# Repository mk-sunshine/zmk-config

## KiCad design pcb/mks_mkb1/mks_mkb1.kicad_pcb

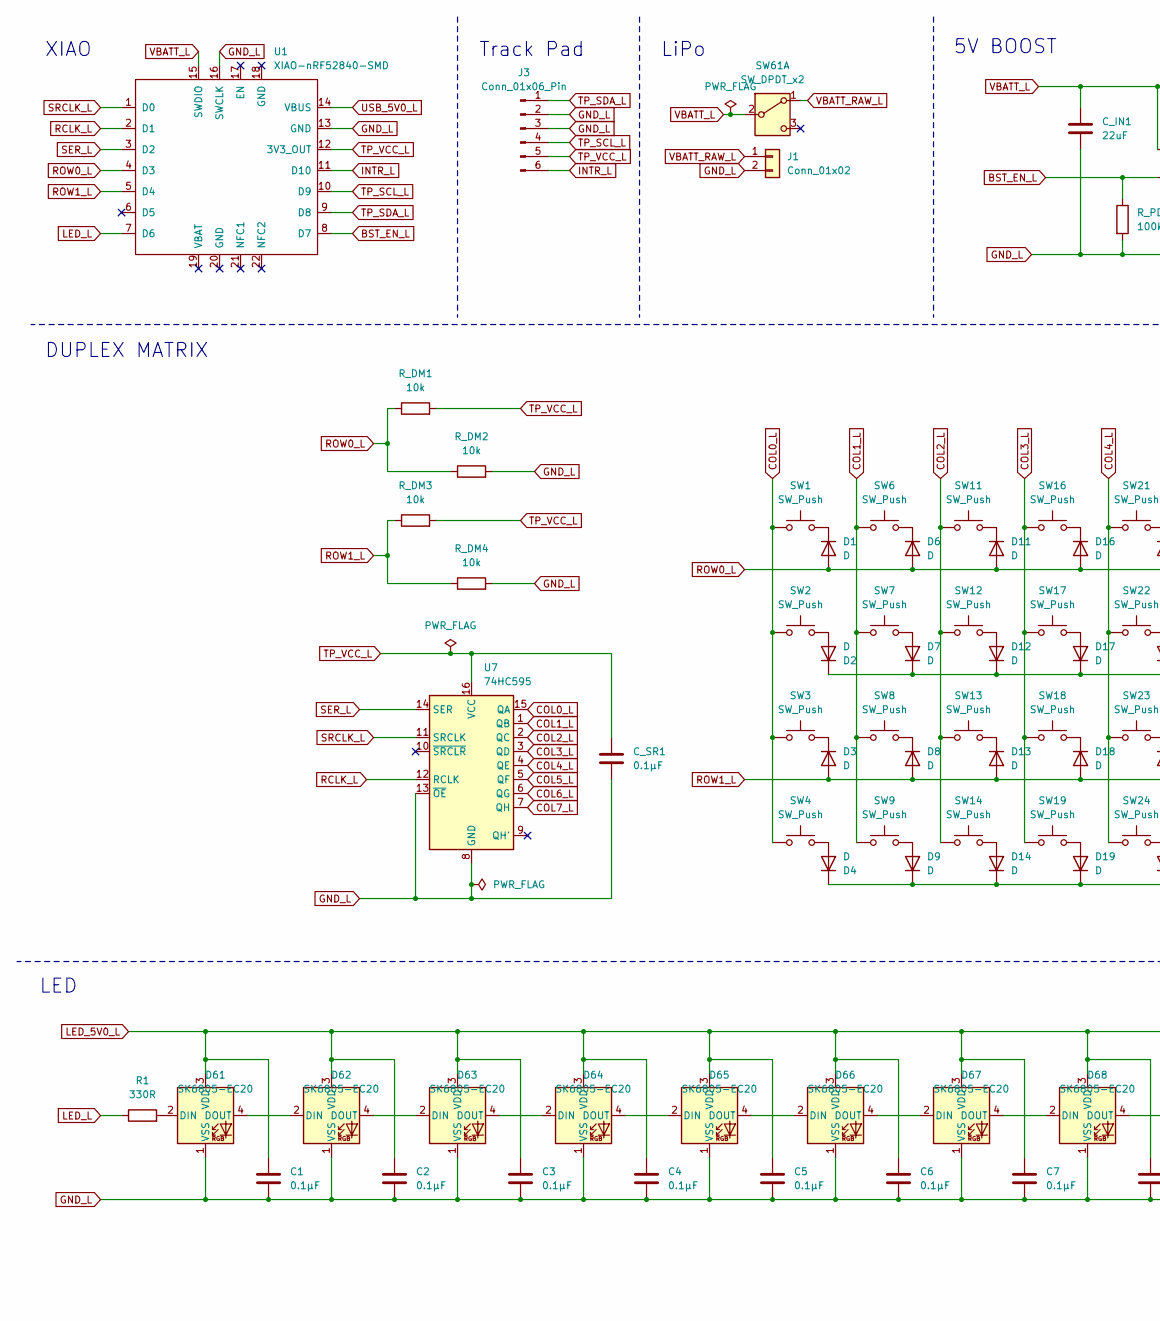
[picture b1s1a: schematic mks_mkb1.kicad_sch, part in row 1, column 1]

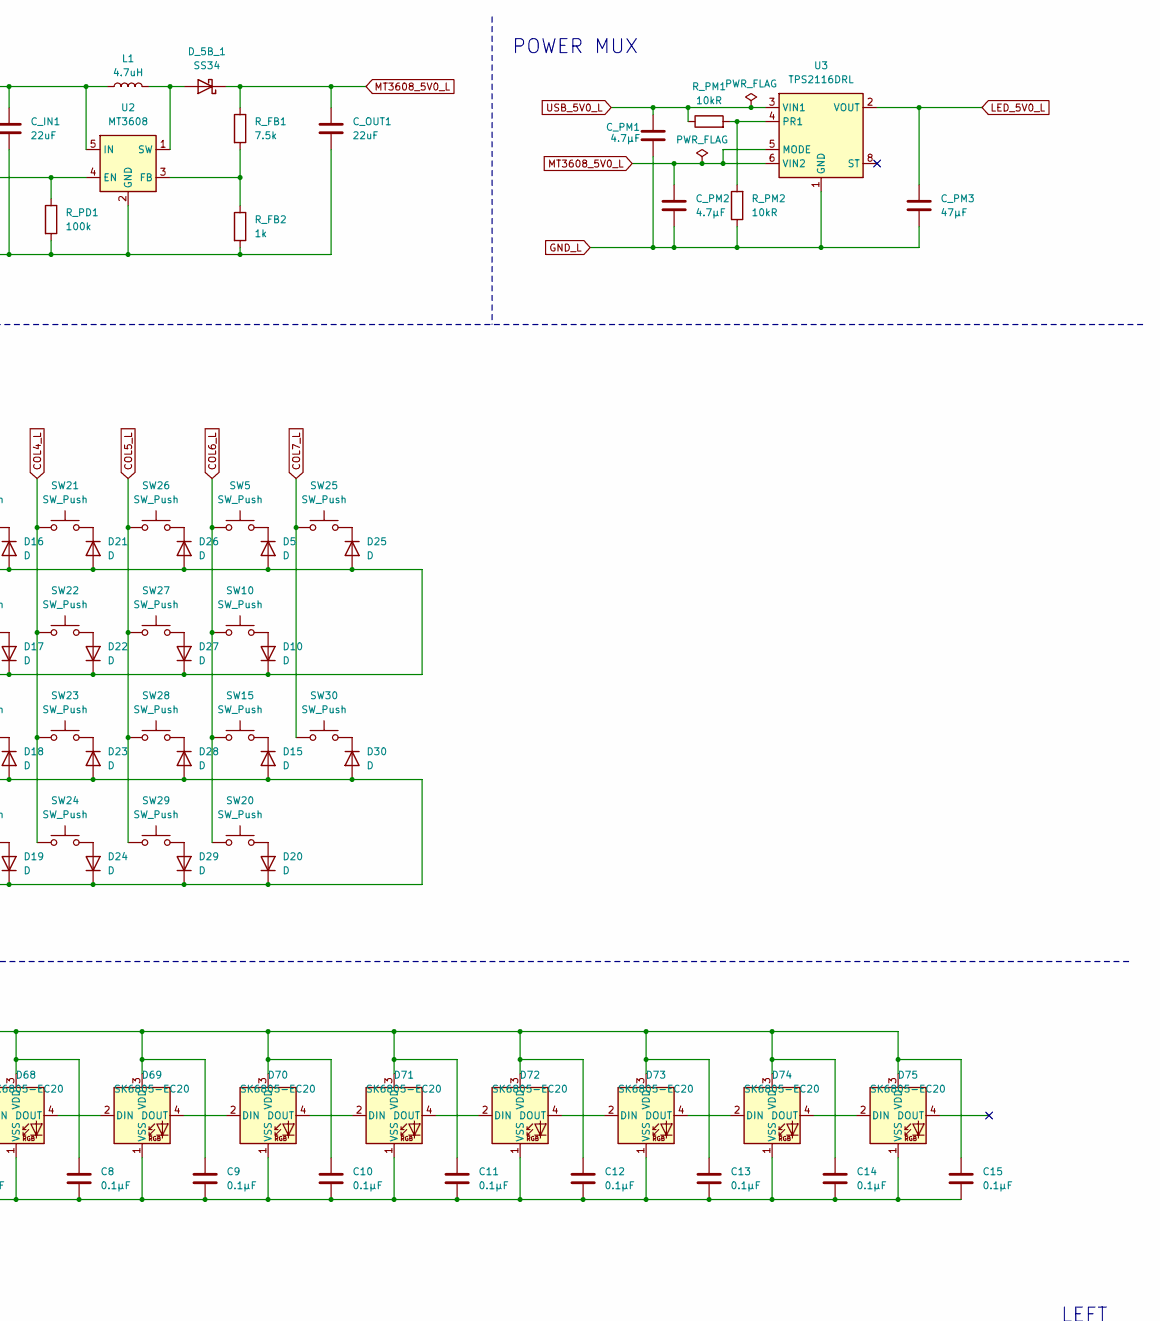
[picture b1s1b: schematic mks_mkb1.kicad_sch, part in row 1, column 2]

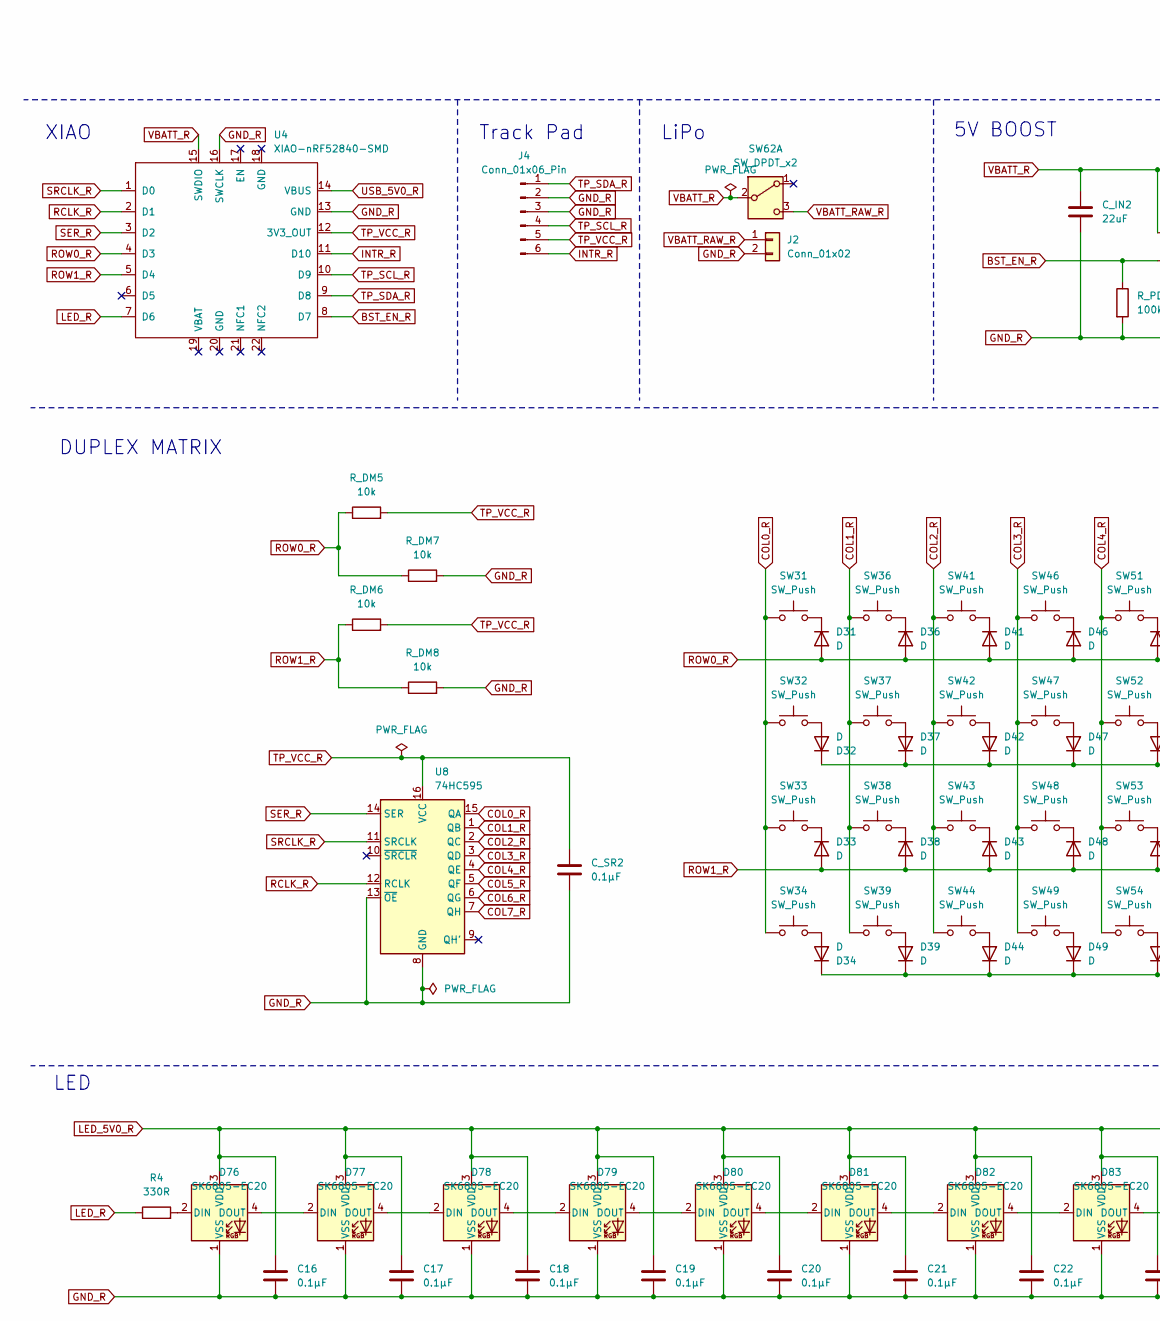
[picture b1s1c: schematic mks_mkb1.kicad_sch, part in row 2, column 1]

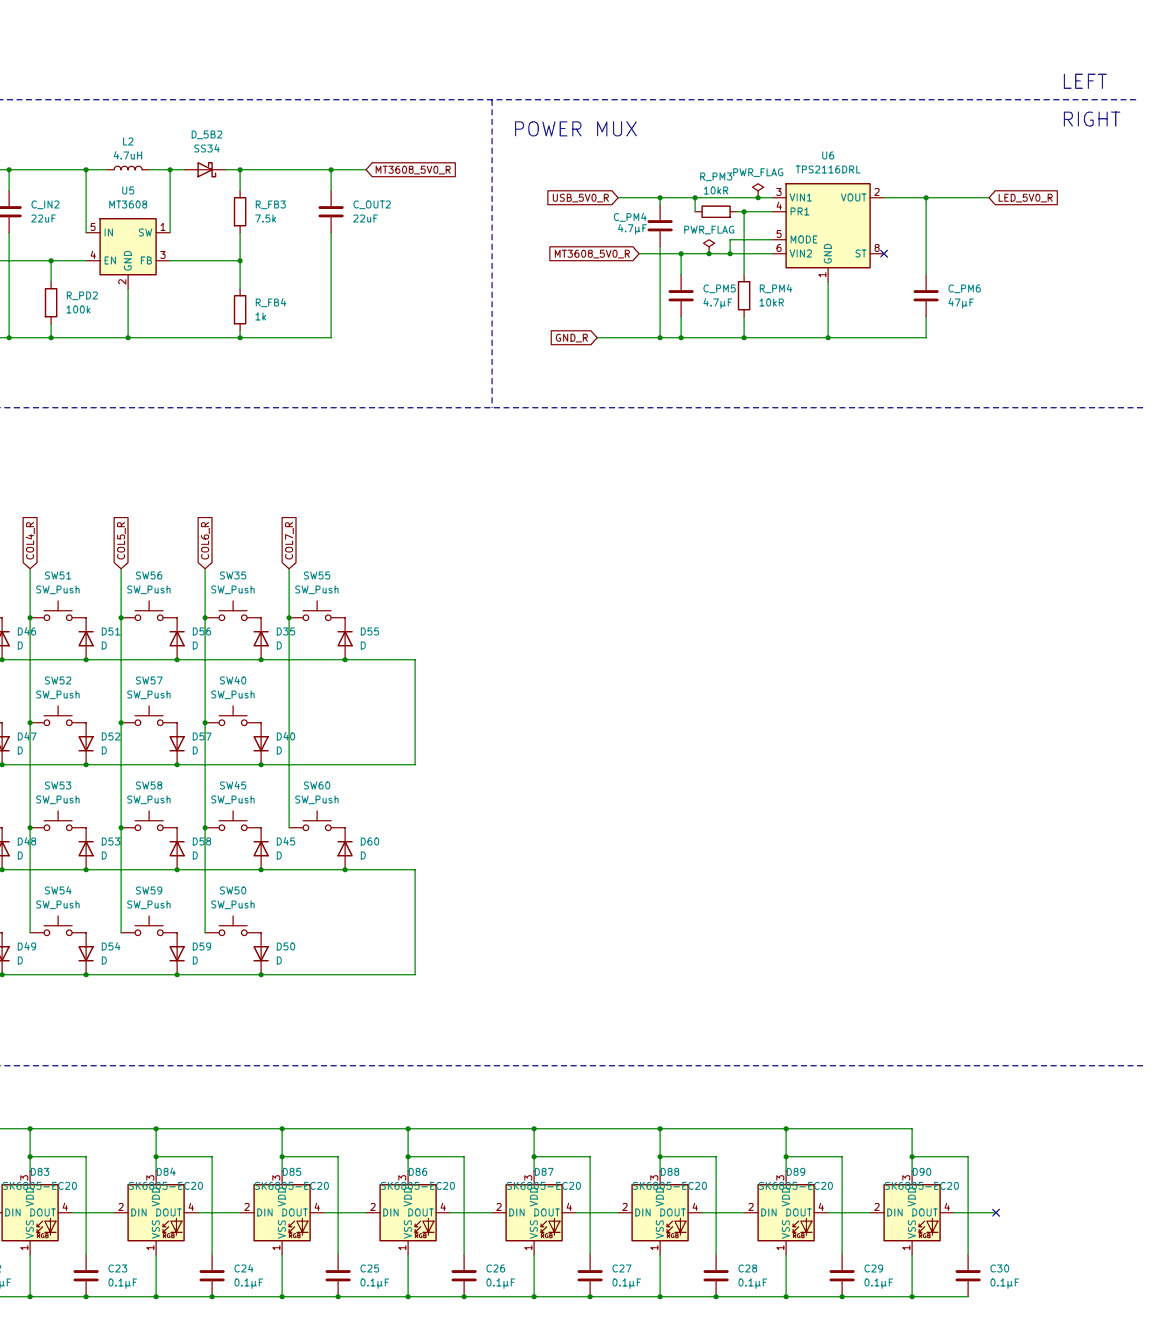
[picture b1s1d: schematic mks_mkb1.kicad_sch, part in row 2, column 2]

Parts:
C1, C2, C3, C4, C5, C6, C7, C8, C9, C10, C11, C12, C13, C14, C15, C16, C17, C18, C19, C20, C21, C22, C23, C24, C25, C26, C27, C28, C29, C30: 0.1µF; C_0603_1608Metric; LCSC C14663
C_IN1, C_IN2: 22uF; C_0805_2012Metric; LCSC C45783
C_OUT1, C_OUT2: 22uF; C_0805_2012Metric; LCSC C45783
C_PM1, C_PM2, C_PM4, C_PM5: 4.7µF; C_0603_1608Metric; LCSC C19666
C_PM3, C_PM6: 47µF; C_0603_1608Metric; LCSC C15852
C_SR1, C_SR2: 0.1µF; C_0603_1608Metric; LCSC C14663
D1, D2, D3, D4, D5, D6, D7, D8, D9, D10, D11, D12, D13, D14, D15, D16, D17, D18, D19, D20, D21, D22, D23, D24, D25, D26, D27, D28, D29, D30, D31, D32, D33, D34, D35, D36, D37, D38, D39, D40, D41, D42, D43, D44, D45, D46, D47, D48, D49, D50, D51, D52, D53, D54, D55, D56, D57, D58, D59, D60: D; D_SOD-123; LCSC C81598
D61, D62, D63, D64, D65, D66, D67, D68, D69, D70, D71, D72, D73, D74, D75, D76, D77, D78, D79, D80, D81, D82, D83, D84, D85, D86, D87, D88, D89, D90: SK6805-EC20
D_5B2, D_5B_1: SS34; D_SMA
J1, J2: Conn_01x02; JST_PH_S2B-PH-K_1x02_P2.00mm_Horizontal
J3, J4: Conn_01x06_Pin; PinSocket_2x03_P2.54mm_Vertical
L1, L2: 4.7uH; L_1210_3225Metric
R1, R4: 330R; R_0603_1608Metric; LCSC C23138
R_DM1, R_DM2, R_DM3, R_DM4, R_DM5, R_DM6, R_DM7, R_DM8: 10k; R_0603_1608Metric; LCSC C25804
R_FB1, R_FB3: 7.5k; R_0603_1608Metric; LCSC C23234
R_FB2, R_FB4: 1k; R_0603_1608Metric; LCSC C21190
R_PD1, R_PD2: 100k; R_0603_1608Metric; LCSC C25803
R_PM1, R_PM2, R_PM3, R_PM4: 10kR; R_0603_1608Metric; LCSC C25804
SW1, SW2, SW3, SW4, SW5, SW6, SW7, SW8, SW9, SW10, SW11, SW12, SW13, SW14, SW15, SW16, SW17, SW18, SW19, SW20, SW21, SW22, SW23, SW24, SW25, SW26, SW27, SW28, SW29, SW30, SW31, SW32, SW33, SW34, SW35, SW36, SW37, SW38, SW39, SW40, SW41, SW42, SW43, SW44, SW45, SW46, SW47, SW48, SW49, SW50, SW51, SW52, SW53, SW54, SW55, SW56, SW57, SW58, SW59, SW60: SW_Push; SW_Kailh_Choc_V1
SW61, SW62: SW_DPDT_x2
U1, U4: XIAO-nRF52840-SMD
U2, U5: MT3608; SOT-23-6
U3, U6: TPS2116DRL; SOT-583-8
U7, U8: 74HC595; SOIC-16_3.9x9.9mm_P1.27mm

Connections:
BST_EN_L: R_PD1.1, U1.8 (D7), U2.4 (EN)
BST_EN_R: R_PD2.1, U4.8 (D7), U5.4 (EN)
COL0_L: SW1.1, SW2.1, SW3.1, SW4.1, U7.15 (QA)
COL0_R: SW31.1, SW32.1, SW33.1, SW34.1, U8.15 (QA)
COL1_L: SW6.1, SW7.1, SW8.1, SW9.1, U7.1 (QB)
COL1_R: SW36.1, SW37.1, SW38.1, SW39.1, U8.1 (QB)
COL2_L: SW11.1, SW12.1, SW13.1, SW14.1, U7.2 (QC)
COL2_R: SW41.1, SW42.1, SW43.1, SW44.1, U8.2 (QC)
COL3_L: SW16.1, SW17.1, SW18.1, SW19.1, U7.3 (QD)
COL3_R: SW46.1, SW47.1, SW48.1, SW49.1, U8.3 (QD)
COL4_L: SW21.1, SW22.1, SW23.1, SW24.1, U7.4 (QE)
COL4_R: SW51.1, SW52.1, SW53.1, SW54.1, U8.4 (QE)
COL5_L: SW26.1, SW27.1, SW28.1, SW29.1, U7.5 (QF)
COL5_R: SW56.1, SW57.1, SW58.1, SW59.1, U8.5 (QF)
COL6_L: SW5.1, SW10.1, SW15.1, SW20.1, U7.6 (QG)
COL6_R: SW35.1, SW40.1, SW45.1, SW50.1, U8.6 (QG)
COL7_L: SW25.1, SW30.1, U7.7 (QH)
COL7_R: SW55.1, SW60.1, U8.7 (QH)
GND_L: C1.2, C2.2, C3.2, C4.2, C5.2, C6.2, C7.2, C8.2, C9.2, C10.2, C11.2, C12.2, C13.2, C14.2, C15.2, C_IN1.2, C_OUT1.2, C_PM1.2, C_PM2.2, C_PM3.2, C_SR1.1, D61.1 (VSS), D62.1 (VSS), D63.1 (VSS), D64.1 (VSS), D65.1 (VSS), D66.1 (VSS), D67.1 (VSS), D68.1 (VSS), D69.1 (VSS), D70.1 (VSS), D71.1 (VSS), D72.1 (VSS), D73.1 (VSS), D74.1 (VSS), D75.1 (VSS), J1.2, J3.2, J3.3, R_DM2.2, R_DM4.2, R_FB2.2, R_PD1.2, R_PM2.1, U1.13 (GND), U1.16 (SWCLK), U2.2 (GND), U3.1 (GND), U7.8 (GND), U7.13 (~OE)
GND_R: C16.2, C17.2, C18.2, C19.2, C20.2, C21.2, C22.2, C23.2, C24.2, C25.2, C26.2, C27.2, C28.2, C29.2, C30.2, C_IN2.2, C_OUT2.2, C_PM4.2, C_PM5.2, C_PM6.2, C_SR2.1, D76.1 (VSS), D77.1 (VSS), D78.1 (VSS), D79.1 (VSS), D80.1 (VSS), D81.1 (VSS), D82.1 (VSS), D83.1 (VSS), D84.1 (VSS), D85.1 (VSS), D86.1 (VSS), D87.1 (VSS), D88.1 (VSS), D89.1 (VSS), D90.1 (VSS), J2.2, J4.2, J4.3, R_DM7.2, R_DM8.2, R_FB4.2, R_PD2.2, R_PM4.1, U4.13 (GND), U4.16 (SWCLK), U5.2 (GND), U6.1 (GND), U8.8 (GND), U8.13 (~OE)
INTR_L: J3.6, U1.11 (D10)
INTR_R: J4.6, U4.11 (D10)
LED_5V0_L: C1.1, C2.1, C3.1, C4.1, C5.1, C6.1, C7.1, C8.1, C9.1, C10.1, C11.1, C12.1, C13.1, C14.1, C15.1, C_PM3.1, D61.3 (VDD), D62.3 (VDD), D63.3 (VDD), D64.3 (VDD), D65.3 (VDD), D66.3 (VDD), D67.3 (VDD), D68.3 (VDD), D69.3 (VDD), D70.3 (VDD), D71.3 (VDD), D72.3 (VDD), D73.3 (VDD), D74.3 (VDD), D75.3 (VDD), U3.2 (VOUT), U3.7 (VOUT)
LED_5V0_R: C16.1, C17.1, C18.1, C19.1, C20.1, C21.1, C22.1, C23.1, C24.1, C25.1, C26.1, C27.1, C28.1, C29.1, C30.1, C_PM6.1, D76.3 (VDD), D77.3 (VDD), D78.3 (VDD), D79.3 (VDD), D80.3 (VDD), D81.3 (VDD), D82.3 (VDD), D83.3 (VDD), D84.3 (VDD), D85.3 (VDD), D86.3 (VDD), D87.3 (VDD), D88.3 (VDD), D89.3 (VDD), D90.3 (VDD), U6.2 (VOUT), U6.7 (VOUT)
LED_L: R1.1, U1.7 (D6)
LED_R: R4.1, U4.7 (D6)
MT3608_5V0_L: C_OUT1.1, C_PM2.1, D_5B_1.1 (K), R_FB1.1, U3.5 (MODE), U3.6 (VIN2)
MT3608_5V0_R: C_OUT2.1, C_PM5.1, D_5B2.1 (K), R_FB3.1, U6.5 (MODE), U6.6 (VIN2)
unnamed: D1.1 (K), SW1.2
unnamed: D2.2 (A), SW2.2
unnamed: D3.1 (K), SW3.2
unnamed: D4.2 (A), SW4.2
unnamed: D5.1 (K), SW5.2
unnamed: D6.1 (K), SW6.2
unnamed: D7.2 (A), SW7.2
unnamed: D8.1 (K), SW8.2
unnamed: D9.2 (A), SW9.2
unnamed: D10.2 (A), SW10.2
unnamed: D11.1 (K), SW11.2
unnamed: D12.2 (A), SW12.2
unnamed: D13.1 (K), SW13.2
unnamed: D14.2 (A), SW14.2
unnamed: D15.1 (K), SW15.2
unnamed: D16.1 (K), SW16.2
unnamed: D17.2 (A), SW17.2
unnamed: D18.1 (K), SW18.2
unnamed: D19.2 (A), SW19.2
unnamed: D20.2 (A), SW20.2
unnamed: D21.1 (K), SW21.2
unnamed: D22.2 (A), SW22.2
unnamed: D23.1 (K), SW23.2
unnamed: D24.2 (A), SW24.2
unnamed: D25.1 (K), SW25.2
unnamed: D26.1 (K), SW26.2
unnamed: D27.2 (A), SW27.2
unnamed: D28.1 (K), SW28.2
unnamed: D29.2 (A), SW29.2
unnamed: D30.1 (K), SW30.2
unnamed: D31.1 (K), SW31.2
unnamed: D32.2 (A), SW32.2
unnamed: D33.1 (K), SW33.2
unnamed: D34.2 (A), SW34.2
unnamed: D35.1 (K), SW35.2
unnamed: D36.1 (K), SW36.2
unnamed: D37.2 (A), SW37.2
unnamed: D38.1 (K), SW38.2
unnamed: D39.2 (A), SW39.2
unnamed: D40.2 (A), SW40.2
unnamed: D41.1 (K), SW41.2
unnamed: D42.2 (A), SW42.2
unnamed: D43.1 (K), SW43.2
unnamed: D44.2 (A), SW44.2
unnamed: D45.1 (K), SW45.2
unnamed: D46.1 (K), SW46.2
unnamed: D47.2 (A), SW47.2
unnamed: D48.1 (K), SW48.2
unnamed: D49.2 (A), SW49.2
unnamed: D50.2 (A), SW50.2
unnamed: D51.1 (K), SW51.2
unnamed: D52.2 (A), SW52.2
unnamed: D53.1 (K), SW53.2
unnamed: D54.2 (A), SW54.2
unnamed: D55.1 (K), SW55.2
unnamed: D56.1 (K), SW56.2
unnamed: D57.2 (A), SW57.2
unnamed: D58.1 (K), SW58.2
unnamed: D59.2 (A), SW59.2
unnamed: D60.1 (K), SW60.2
unnamed: D61.2 (DIN), R1.2
unnamed: D61.4 (DOUT), D62.2 (DIN)
unnamed: D62.4 (DOUT), D63.2 (DIN)
unnamed: D63.4 (DOUT), D64.2 (DIN)
unnamed: D64.4 (DOUT), D65.2 (DIN)
unnamed: D65.4 (DOUT), D66.2 (DIN)
unnamed: D66.4 (DOUT), D67.2 (DIN)
unnamed: D67.4 (DOUT), D68.2 (DIN)
unnamed: D68.4 (DOUT), D69.2 (DIN)
unnamed: D69.4 (DOUT), D70.2 (DIN)
unnamed: D70.4 (DOUT), D71.2 (DIN)
unnamed: D71.4 (DOUT), D72.2 (DIN)
unnamed: D72.4 (DOUT), D73.2 (DIN)
unnamed: D73.4 (DOUT), D74.2 (DIN)
unnamed: D74.4 (DOUT), D75.2 (DIN)
unnamed: D76.2 (DIN), R4.2
unnamed: D76.4 (DOUT), D77.2 (DIN)
unnamed: D77.4 (DOUT), D78.2 (DIN)
unnamed: D78.4 (DOUT), D79.2 (DIN)
unnamed: D79.4 (DOUT), D80.2 (DIN)
unnamed: D80.4 (DOUT), D81.2 (DIN)
unnamed: D81.4 (DOUT), D82.2 (DIN)
unnamed: D82.4 (DOUT), D83.2 (DIN)
unnamed: D83.4 (DOUT), D84.2 (DIN)
unnamed: D84.4 (DOUT), D85.2 (DIN)
unnamed: D85.4 (DOUT), D86.2 (DIN)
unnamed: D86.4 (DOUT), D87.2 (DIN)
unnamed: D87.4 (DOUT), D88.2 (DIN)
unnamed: D88.4 (DOUT), D89.2 (DIN)
unnamed: D89.4 (DOUT), D90.2 (DIN)
unnamed: D_5B2.2 (A), L2.2, U5.1 (SW)
unnamed: D_5B_1.2 (A), L1.2, U2.1 (SW)
unnamed: R_FB1.2, R_FB2.1, U2.3 (FB)
unnamed: R_PM1.2, R_PM2.2, U3.4 (PR1)
unnamed: R_FB3.2, R_FB4.1, U5.3 (FB)
unnamed: R_PM3.2, R_PM4.2, U6.4 (PR1)
RCLK_L: U1.2 (D1), U7.12 (RCLK)
RCLK_R: U4.2 (D1), U8.12 (RCLK)
ROW0_L: D1.2 (A), D2.1 (K), D5.2 (A), D6.2 (A), D7.1 (K), D10.1 (K), D11.2 (A), D12.1 (K), D16.2 (A), D17.1 (K), D21.2 (A), D22.1 (K), D25.2 (A), D26.2 (A), D27.1 (K), R_DM1.1, R_DM2.1, U1.4 (D3)
ROW0_R: D31.2 (A), D32.1 (K), D35.2 (A), D36.2 (A), D37.1 (K), D40.1 (K), D41.2 (A), D42.1 (K), D46.2 (A), D47.1 (K), D51.2 (A), D52.1 (K), D55.2 (A), D56.2 (A), D57.1 (K), R_DM5.1, R_DM7.1, U4.4 (D3)
ROW1_L: D3.2 (A), D4.1 (K), D8.2 (A), D9.1 (K), D13.2 (A), D14.1 (K), D15.2 (A), D18.2 (A), D19.1 (K), D20.1 (K), D23.2 (A), D24.1 (K), D28.2 (A), D29.1 (K), D30.2 (A), R_DM3.1, R_DM4.1, U1.5 (D4)
ROW1_R: D33.2 (A), D34.1 (K), D38.2 (A), D39.1 (K), D43.2 (A), D44.1 (K), D45.2 (A), D48.2 (A), D49.1 (K), D50.1 (K), D53.2 (A), D54.1 (K), D58.2 (A), D59.1 (K), D60.2 (A), R_DM6.1, R_DM8.1, U4.5 (D4)
SER_L: U1.3 (D2), U7.14 (SER)
SER_R: U4.3 (D2), U8.14 (SER)
SRCLK_L: U1.1 (D0), U7.11 (SRCLK)
SRCLK_R: U4.1 (D0), U8.11 (SRCLK)
TP_SCL_L: J3.4, U1.10 (D9)
TP_SCL_R: J4.4, U4.10 (D9)
TP_SDA_L: J3.1, U1.9 (D8)
TP_SDA_R: J4.1, U4.9 (D8)
TP_VCC_L: C_SR1.2, J3.5, R_DM1.2, R_DM3.2, U1.12 (3V3_OUT), U7.16 (VCC)
TP_VCC_R: C_SR2.2, J4.5, R_DM5.2, R_DM6.2, U4.12 (3V3_OUT), U8.16 (VCC)
USB_5V0_L: C_PM1.1, R_PM1.1, U1.14 (VBUS), U3.3 (VIN1)
USB_5V0_R: C_PM4.1, R_PM3.1, U4.14 (VBUS), U6.3 (VIN1)
VBATT_L: C_IN1.1, L1.1, SW61.2 (B), U1.15 (SWDIO), U2.5 (IN)
VBATT_R: C_IN2.1, L2.1, SW62.2 (B), U4.15 (SWDIO), U5.5 (IN)
VBATT_RAW_L: J1.1, SW61.1 (A)
VBATT_RAW_R: J2.1, SW62.3 (C)

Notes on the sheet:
LiPo
XIAO
5V BOOST
POWER MUX
DUPLEX MATRIX
LED
LEFT
RIGHT
Track Pad

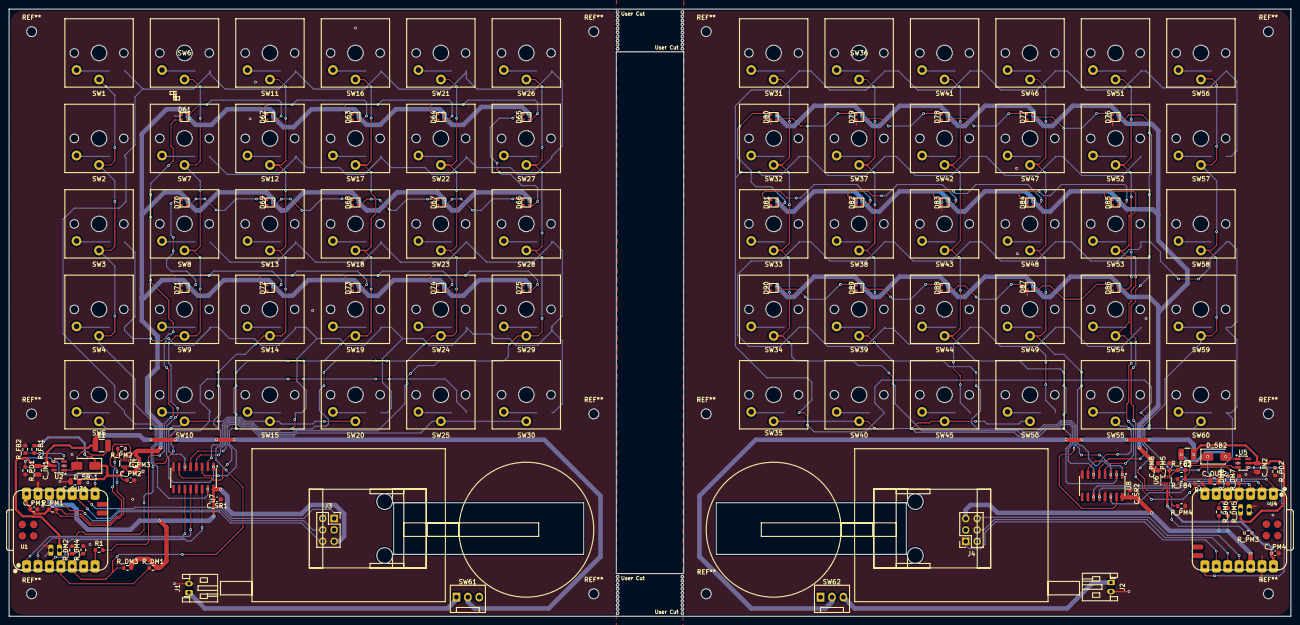
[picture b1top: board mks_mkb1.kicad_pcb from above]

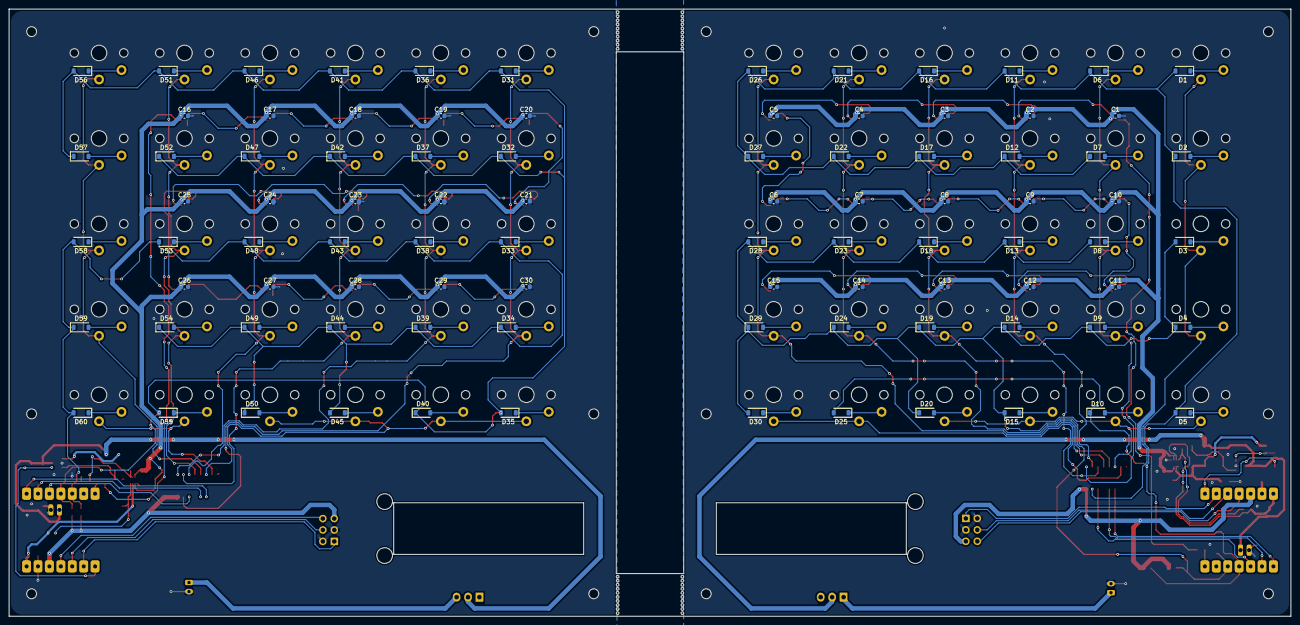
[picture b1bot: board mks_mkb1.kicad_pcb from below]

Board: 2 copper layers, 285.0 x 135.0 mm, 230 parts (90 on the bottom side), 146 nets.

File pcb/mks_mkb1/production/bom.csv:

Designator,Footprint,Quantity,Value,LCSC Part #
"C1, C10, C11, C12, C13, C14, C15, C16, C17, C18, C19, C2, C20, C21, C22, C23, C24, C25, C26, C27, C28, C29, C3, C30, C4, C5, C6, C7, C8, C9, C_SR1, C_SR2",0603,32,0.1µF,C14663
"C_IN1, C_IN2, C_OUT1, C_OUT2",0805,4,22uF,C45783
"C_PM1, C_PM2, C_PM4, C_PM5",0603,4,4.7µF,C19666
"C_PM3, C_PM6",0603,2,47µF,C15852
"D1, D10, D11, D12, D13, D14, D15, D16, D17, D18, D19, D2, D20, D21, D22, D23, D24, D25, D26, D27, D28, D29, D3, D30, D31, D32, D33, D34, D35, D36, D37, D38, D39, D4, D40, D41, D42, D43, D44, D45, D46, D47, D48, D49, D5, D50, D51, D52, D53, D54, D55, D56, D57, D58, D59, D6, D60, D7, D8, D9",D_SOD-123,60,D,C81598
"D61, D62, D63, D64, D65, D66, D67, D68, D69, D70, D71, D72, D73, D74, D75, D76, D77, D78, D79, D80, D81, D82, D83, D84, D85, D86, D87, D88, D89, D90",SK6805-EC20,30,SK6805-EC20,
"D_5B2, D_5B_1",D_SMA,2,SS34,
"J1, J2",JST_PH_S2B-PH-K_1x02_P2.00mm_Horizontal,2,Conn_01x02,
"J3, J4",PinSocket_2x03_P2.54mm_Vertical,2,Conn_01x06_Pin,
"L1, L2",1210,2,4.7uH,
"R1, R4",0603,2,330R,C23138 
"R_DM2, R_DM4, R_DM7, R_DM8",0603,4,10k,C25804
"R_FB1, R_FB3",0603,2,7.5k,C23234
"R_FB2, R_FB4",0603,2,1k,C21190
"R_PD1, R_PD2",0603,2,100k,C25803
"R_PM1, R_PM2, R_PM3, R_PM4",0603,4,10kR,C25804
"SW1, SW10, SW11, SW12, SW13, SW14, SW15, SW16, SW17, SW18, SW19, SW2, SW20, SW21, SW22, SW23, SW24, SW25, SW26, SW27, SW28, SW29, SW3, SW30, SW31, SW32, SW33, SW34, SW35, SW36, SW37, SW38, SW39, SW4, SW40, SW41, SW42, SW43, SW44, SW45, SW46, SW47, SW48, SW49, SW5, SW50, SW51, SW52, SW53, SW54, SW55, SW56, SW57, SW58, SW59, SW6, SW60, SW7, SW8, SW9",SW_Kailh_Choc_V1,60,SW_Push,
"SW61, SW62",FanPinHeader_1x03_P2.54mm_Vertical,2,SW_DPDT_x2,
"U1, U4",XIAO-nRF52840-SMD,2,XIAO-nRF52840-SMD,
"U2, U5",SOT-23-6,2,MT3608,
"U3, U6",SOT-583-8,2,TPS2116DRL,
"U7, U8",SOIC-16_3.9x9.9mm_P1.27mm,2,74HC595,
